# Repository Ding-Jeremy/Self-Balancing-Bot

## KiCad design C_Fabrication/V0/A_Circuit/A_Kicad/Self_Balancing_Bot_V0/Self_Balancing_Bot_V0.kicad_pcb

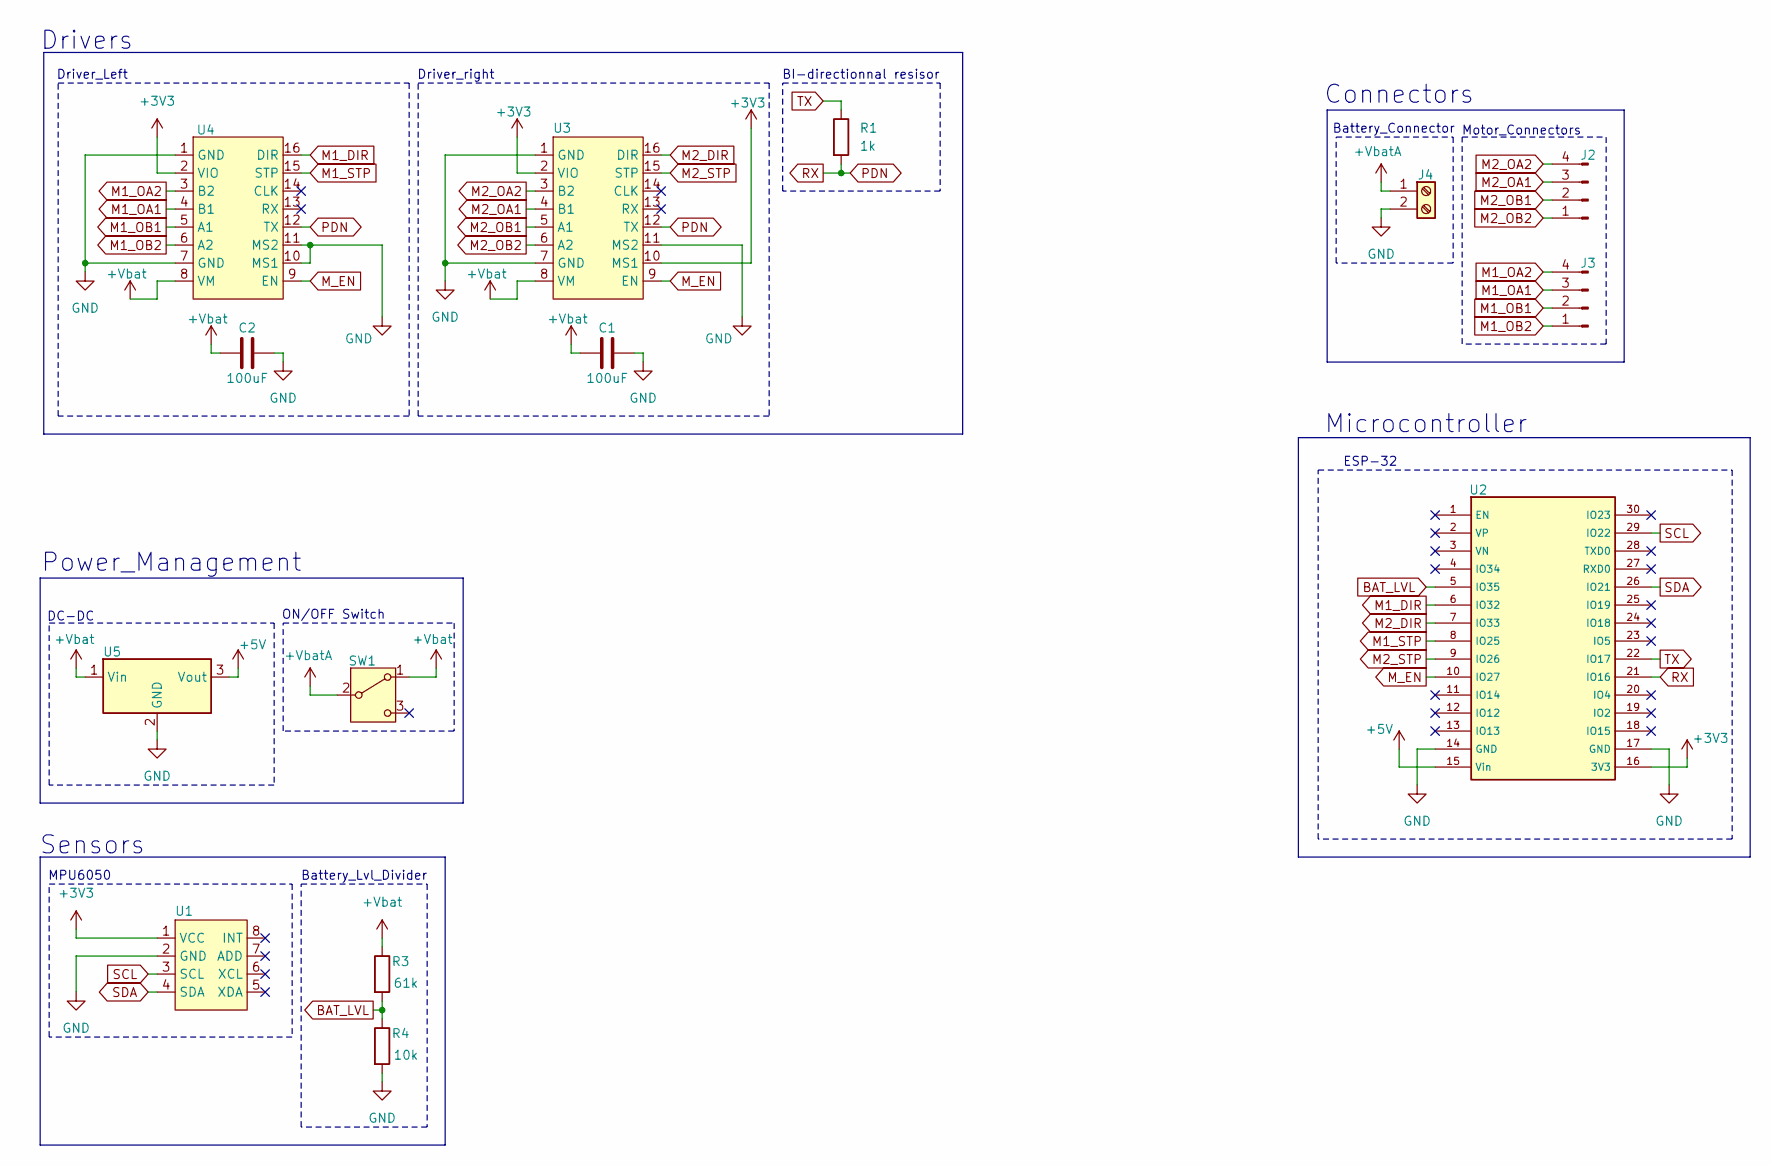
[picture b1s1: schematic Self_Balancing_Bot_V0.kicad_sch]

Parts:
C1, C2: 100uF; C_Elec_6.3x5.8
J2, J3: Conn_01x04_Pin; PinHeader_1x04_P2.54mm_Vertical
J4: Screw_Terminal_01x02; TerminalBlock_Phoenix_MKDS-1,5-2_1x02_P5.00mm_Horizontal
R1: 1k; R_1206_3216Metric
R3: 61k; R_1206_3216Metric
R4: 10k; R_1206_3216Metric
SW1: SW_SPDT; SW_Slide_SPDT_Angled_CK_OS102011MA1Q
U1: MPU6050
U2: ESP32_DEVKITC_30P
U3, U4: TMC2130
U5: TSR1-2450E; Converter_DCDC_TRACO_TSR1-xxxxE_THT

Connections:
+3V3: U1.1 (VCC), U2.16 (3V3), U3.2 (VIO), U3.10 (MS1), U4.2 (VIO)
+5V: U2.15 (Vin), U5.3 (Vout)
+Vbat: C1.1, C2.1, R3.1, SW1.1 (A), U3.8 (VM), U4.8 (VM), U5.1 (Vin)
+VbatA: J4.1, SW1.2 (B)
BAT_LVL: R3.2, R4.1, U2.5 (IO35)
GND: C1.2, C2.2, J4.2, R4.2, U1.2 (GND), U2.14 (GND), U2.17 (GND), U3.1 (GND), U3.7 (GND), U3.11 (MS2), U4.1 (GND), U4.7 (GND), U4.10 (MS1), U4.11 (MS2), U5.2 (GND)
M1_DIR: U2.6 (IO32), U4.16 (DIR)
M1_OA1: J3.3, U4.4 (B1)
M1_OA2: J3.4, U4.3 (B2)
M1_OB1: J3.2, U4.5 (A1)
M1_OB2: J3.1, U4.6 (A2)
M1_STP: U2.8 (IO25), U4.15 (STP)
M2_DIR: U2.7 (IO33), U3.16 (DIR)
M2_OA1: J2.3, U3.4 (B1)
M2_OA2: J2.4, U3.3 (B2)
M2_OB1: J2.2, U3.5 (A1)
M2_OB2: J2.1, U3.6 (A2)
M2_STP: U2.9 (IO26), U3.15 (STP)
M_EN: U2.10 (IO27), U3.9 (EN), U4.9 (EN)
PDN: R1.2, U2.21 (IO16), U3.12 (TX), U4.12 (TX)
SCL: U1.3 (SCL), U2.29 (IO22)
SDA: U1.4 (SDA), U2.26 (IO21)
TX: R1.1, U2.22 (IO17)

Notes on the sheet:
Battery_Connector
ON/OFF Switch
DC-DC
Sensors
Power_Management
Driver_right
Connectors
Microcontroller
Driver_Left
Motor_Connectors
Drivers
ESP-32
MPU6050
BI-directionnal resisor
Battery_Lvl_Divider

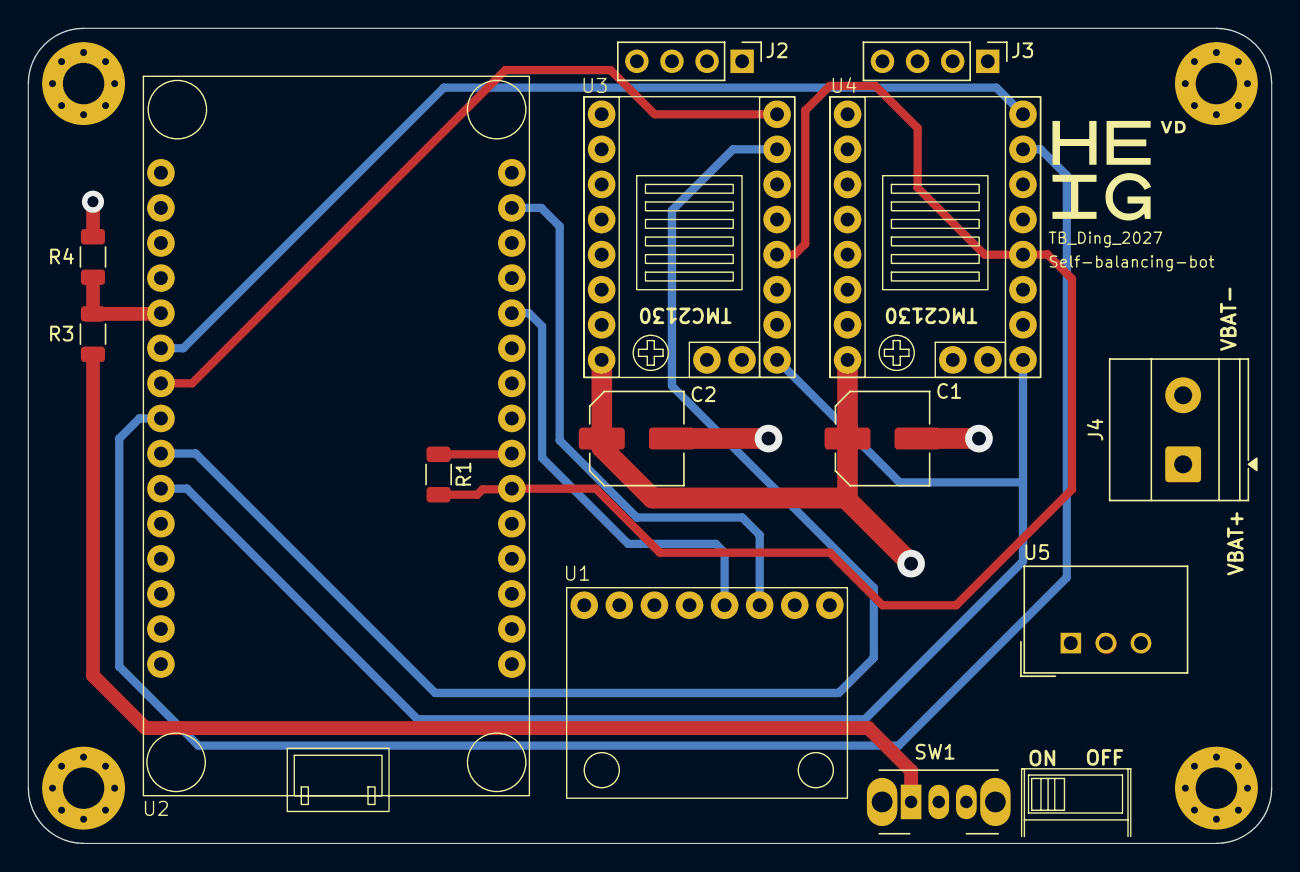
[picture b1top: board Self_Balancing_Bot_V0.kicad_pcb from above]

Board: 4 copper layers, 90.0 x 59.0 mm, 14 parts (0 on the bottom side), 23 nets.

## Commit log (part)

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2026-02-23 First commit, add files
2026-02-23 First Hello World
2026-02-23 First readings with the MPU
2026-05-28 Added ESP32 project, firmware
2026-05-28 Implementation of wifi, ws, littlefs, (file management) and server
2026-05-29 Communication with TMC2226
2026-05-30 Trying TMC2226 communication
2026-05-30 Tmc upgrade
2026-05-31 Add step pin
2026-05-31 Successfull com, modified bitfields
2026-06-01 Registers of TMC2226 modifications
2026-06-01 implement mpu sensor
2026-06-02 Added PID regulator, rm functions in TMC2226
2026-06-02 Tries start of balancing
2026-06-03 modified regulator parameters
2026-06-03 upgrade PID, added functions on web app
2026-06-03 upgraded website, added PID tuner
2026-06-04 Upgraded website, modified PID dimensions
2026-06-04 modified PID (position)
2026-06-17 Added TMC2226 class
2026-06-18 Added record function, re-implemented speed (PID)
2026-06-23 Added battery function
2026-06-23 Project Tree modif
2026-06-23 Added new files
2026-06-23 Created Latex report
2026-06-23 Modified Report Layout
2026-06-23 Redaction of component's choices
2026-06-23 Fixing nomenclature
2026-06-24 Added planning, modified PID, (back to acceleration)
2026-06-24 Modified Resisors Ratio, Max wheel acceleration, Motors off mode
2026-06-25 Corrected nomenclature, glossary compilation error
2026-06-25 Measurements, Redaction
2026-06-25 Update Glossary, Electronic developpement, programmation
2026-06-25 Update Electronic design redaction, stepper current
2026-06-25 Updated nomenclature, Measurements, Physical principle
2026-06-25 updated nomenclature
2026-06-29 Added Matlab files, Component's bills, DrawIO schematics, KiCad Files
2026-06-29 Component's choices, Electronic design
2026-06-30 updated planning, update component's choice, electronics design
2026-06-30 End of component's choice, added bib references
2026-06-30 Electronics redaction
